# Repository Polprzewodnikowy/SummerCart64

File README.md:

# SummerCart64 - a fully open source N64 flashcart

**For non-technical description of the SummerCart64, please head to the https://summercart64.dev website!**

## Features

 - **ROM and Save Memory On-board**
   - 64 MiB SDRAM memory for game and save data (enough memory to support every retail game without compromise)
   - 16 MiB FLASH memory for bootloader and extended game data (with extended memory flashcart supports game ROMs up to 78 MiB)

 - **Game Saves**
   - EEPROM 4k/16k, SRAM and FlashRAM save types with an automatic writeback to the SD card (no reset button press required)

 - **Hardware-Dependent Game Features**
   - 64DD add-on emulation
   - Battery backed real time clock (RTC)

 - **Menu**
   - Dedicated open source menu written specifically for this flashcart - [N64FlashcartMenu](https://github.com/Polprzewodnikowy/N64FlashcartMenu)

 - **Game Development**
   - ~23.8 MiB/s peak transfer rate SD card interface
   - ~23.8 MiB/s peak transfer rate USB interface for data upload/download and debug functionality
   - PC app to access the flashcart features:
     - Game/save data upload/download
     - Feature enable control
     - Debug terminal
     - Access to the SD card
     - Firmware update
   - [UNFLoader](https://github.com/buu342/N64-UNFLoader) support
   - IS-Viewer 64 debug interface (fixed 64 kiB buffer with a movable base address)
   - 8 kiB on-chip buffer for general use
   - Status LED and button for general use
   - [UltraCIC_C](https://github.com/jago85/UltraCIC_C) emulation with automatic region switching and programmable seed/checksum values
   - N64 bootloader with support for IPL3 registers spoofing and loading menu from SD card

 - **Cartridge Production**
   - Initial programming via UART header or via dedicated JTAG/SWD interfaces
   - 3D printable shell

---

## Documentation

- [Quick startup guide](./docs/00_quick_startup_guide.md)
- [Memory map](./docs/01_memory_map.md)
- [N64 commands](./docs/02_n64_commands.md)
- [USB interface](./docs/03_usb_interface.md)
- [Config options](./docs/04_config_options.md)
- [FW and SW info](./docs/05_fw_and_sw_info.md)
- [Build guide](./docs/06_build_guide.md)

---

## How do I get one?

Most up to date information about purchasing/manufacturing options is available on https://summercart64.dev website!

If you want to order it yourself then I've prepared all necessary manufacturing files on the [PCBWay Shared Project](https://www.pcbway.com/project/member/shareproject/?bmbno=1046ED64-8AEE-44) site.

**Be careful**: this is an advanced project and it is assumed that you have enough knowledge about electronics.
Selecting wrong options or giving PCB manufacturer wrong information might result in an undesired time and/or money loss.
Boards also come unprogrammed from the manufacturer - you need to do **initial programming step** yourself after receiving the board.
**Price of the components is not included in the initial quote at the checkout** - manufacturer will contact you later with updated price.
To avoid problems _**please**_ read **both** [build guide](./docs/06_build_guide.md) and description on the shared project page **in full**.
If you have even slightest doubt about the ordering or programming process, it is better to leave it to someone experienced - ask in the [N64brew Discord server](https://discord.gg/8VNMKhxqQn) if that's the case.

**Full disclosure**: for every order made through [this link](https://www.pcbway.com/project/member/shareproject/?bmbno=1046ED64-8AEE-44) I will receive 10% of PCB manufacturing and PCB assembly service cost (price of the components is not included in the split). This is a great way of supporting further project development.

If you don't need a physical product but still want to support me then check the sponsor links on the [official website](https://summercart64.dev).

---

## High-level flashcart block diagram

---

## Finished example

---

## Acknowledgement

This project wouldn't be possible without these contributions:

- [64drive](https://64drive.retroactive.be) ([archived](https://web.archive.org/web/20240406215731/https://64drive.retroactive.be/)) orders being on permanent hold long before creating this repository.
- [EverDrive-64 X7](https://krikzz.com/our-products/cartridges/ed64x7.html) being disappointment for homebrew development (slow USB upload, unjustified price and overcomplicated SD card access).
  - Context: Both aforementioned products were priced at $199 in 2020. 64drive features made it a vastly more useful tool for homebrew development.
    Since then, 64drive had never been restocked and EverDrive-64 X7 price was lowered to $159 (as of May 2024).
- [Jan Goldacker (@jago85)](https://github.com/jago85) and his projects:
  - [Brutzelkarte](https://github.com/jago85/Brutzelkarte_FPGA) providing solid base for starting this project and sparking hope for true open source N64 flashcarts.
  - [UltraCIC_C](https://github.com/jago85/UltraCIC_C) reimplementation for easy integration in modern microcontrollers. Thanks also goes to everyone involved in N64 CIC reverse engineering.
- [N64brew](https://discord.gg/WqFgNWf) Discord server community being very helpful during flashcart development.
- [FatFs](http://elm-chan.org/fsw/ff/00index_e.html) FAT32/exFAT library being easiest to integrate in embedded environment.
- [Yakumono's (@LuigiBlood)](https://twitter.com/LuigiBlood) extensive [64DD documentation](https://github.com/LuigiBlood/64dd/wiki) and its implementation in various emulators.
- [Libdragon](https://github.com/DragonMinded/libdragon) open source N64 SDK project and its developers.
- [SERV](https://github.com/olofk/serv) bit-serial 32-bit RISC-V CPU soft core.

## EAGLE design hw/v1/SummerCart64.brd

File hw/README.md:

# SummerCart64 Hardware

Schematics and PCB design for SummerCart64 done in Autodesk Eagle software.

## TODO

- Expand documentation

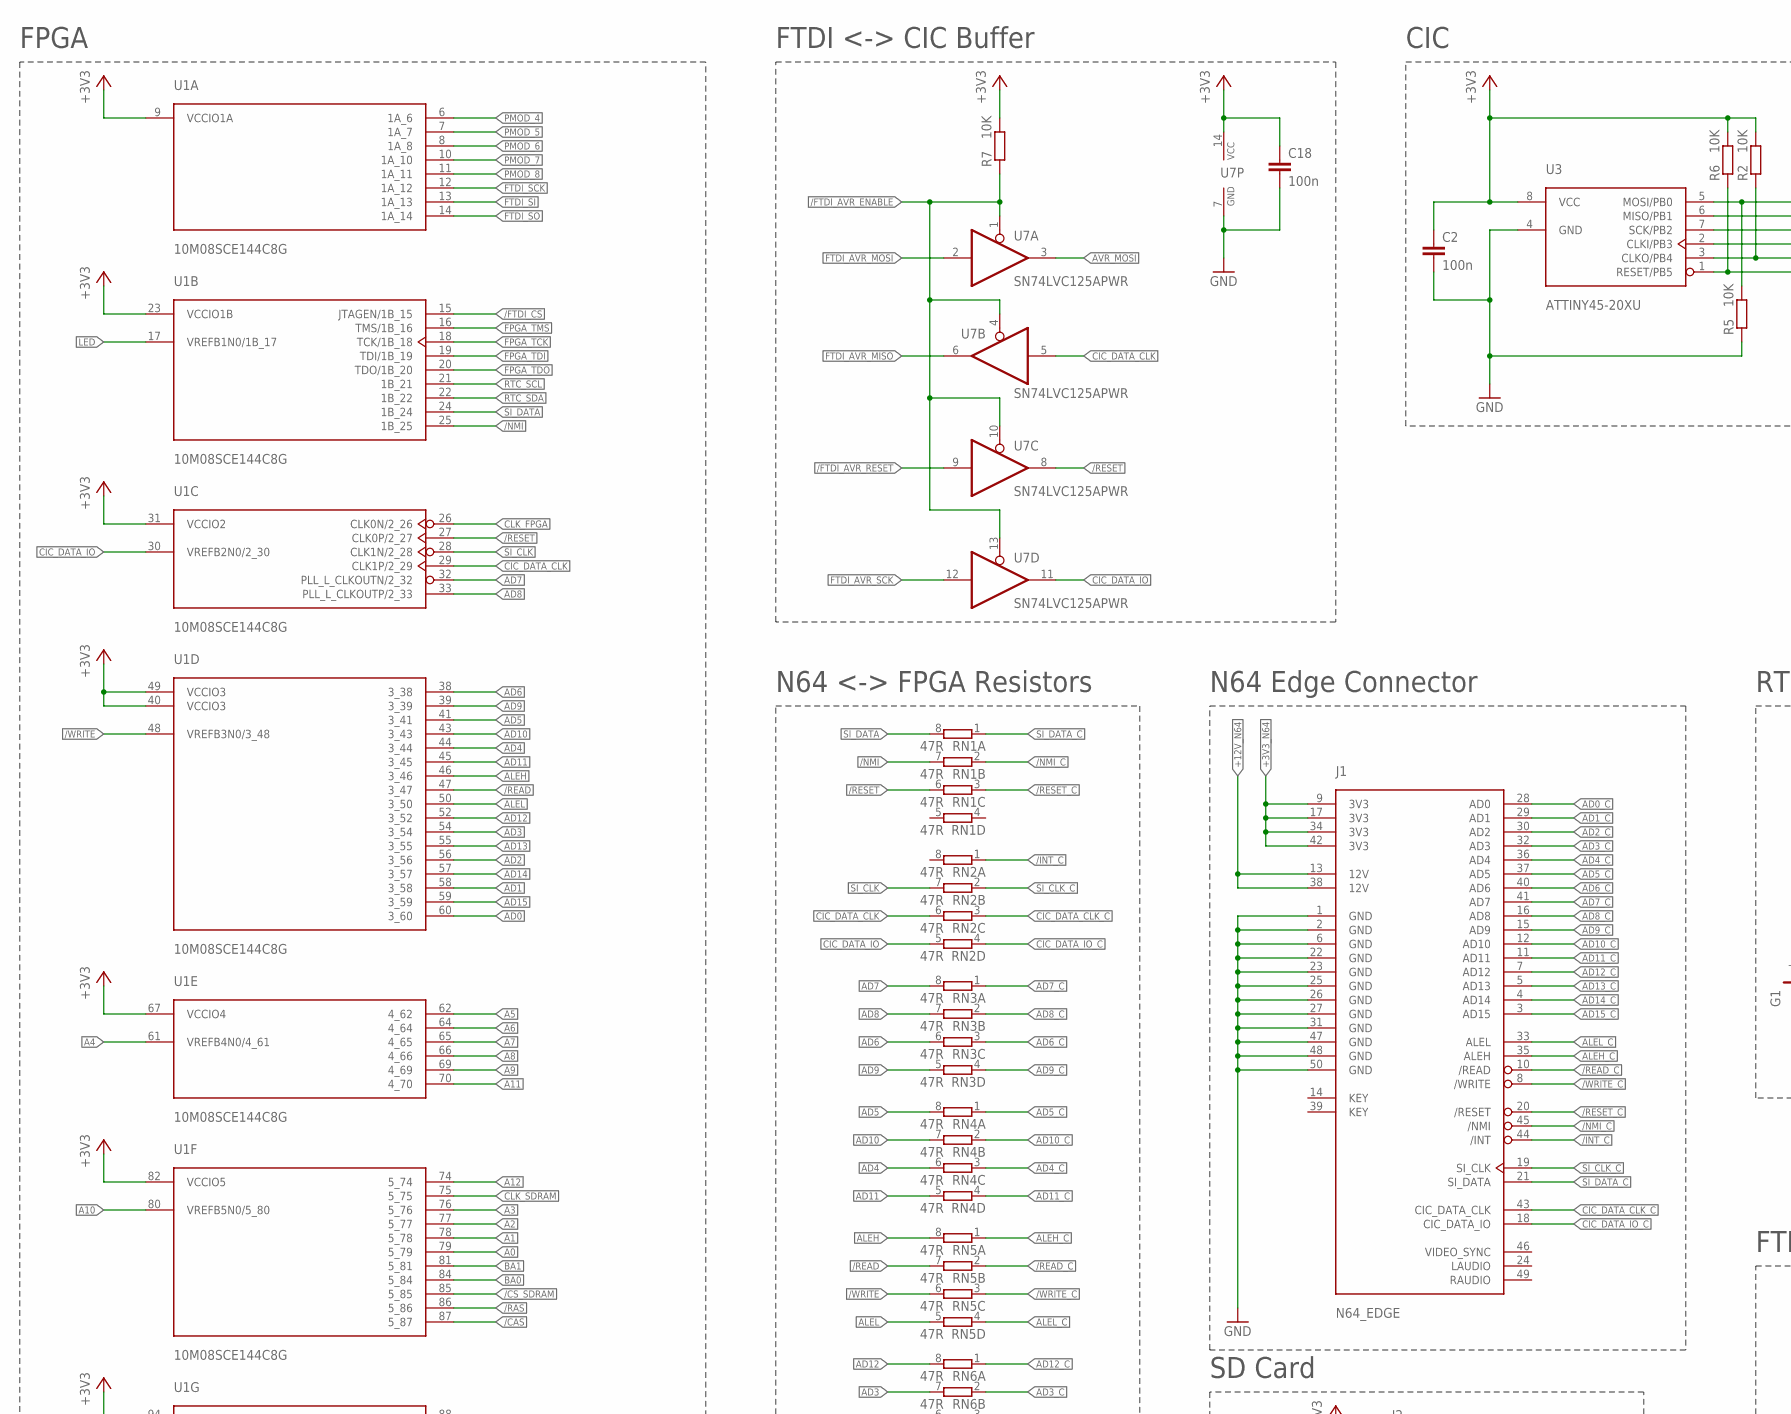
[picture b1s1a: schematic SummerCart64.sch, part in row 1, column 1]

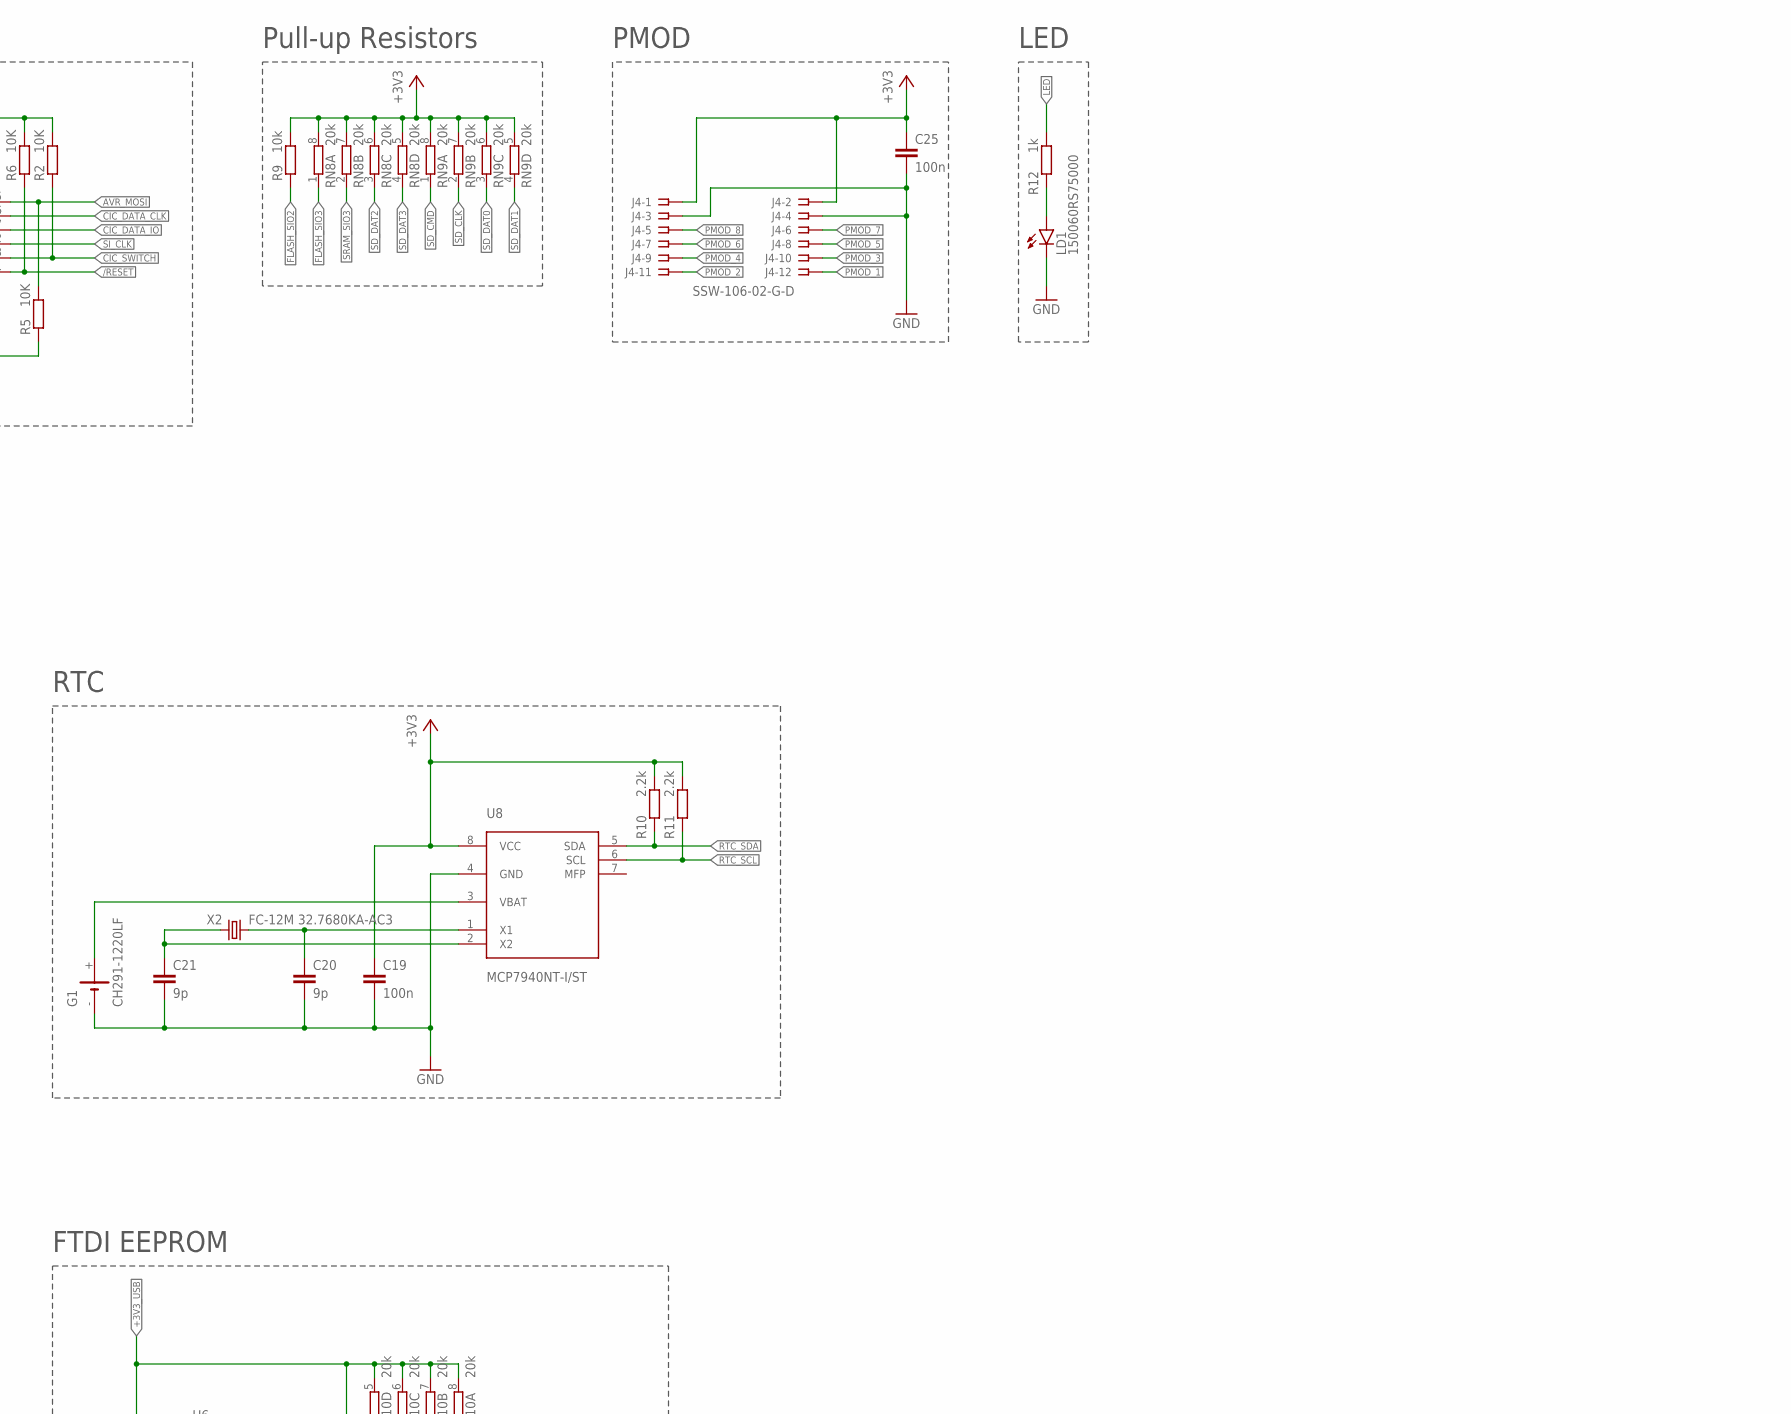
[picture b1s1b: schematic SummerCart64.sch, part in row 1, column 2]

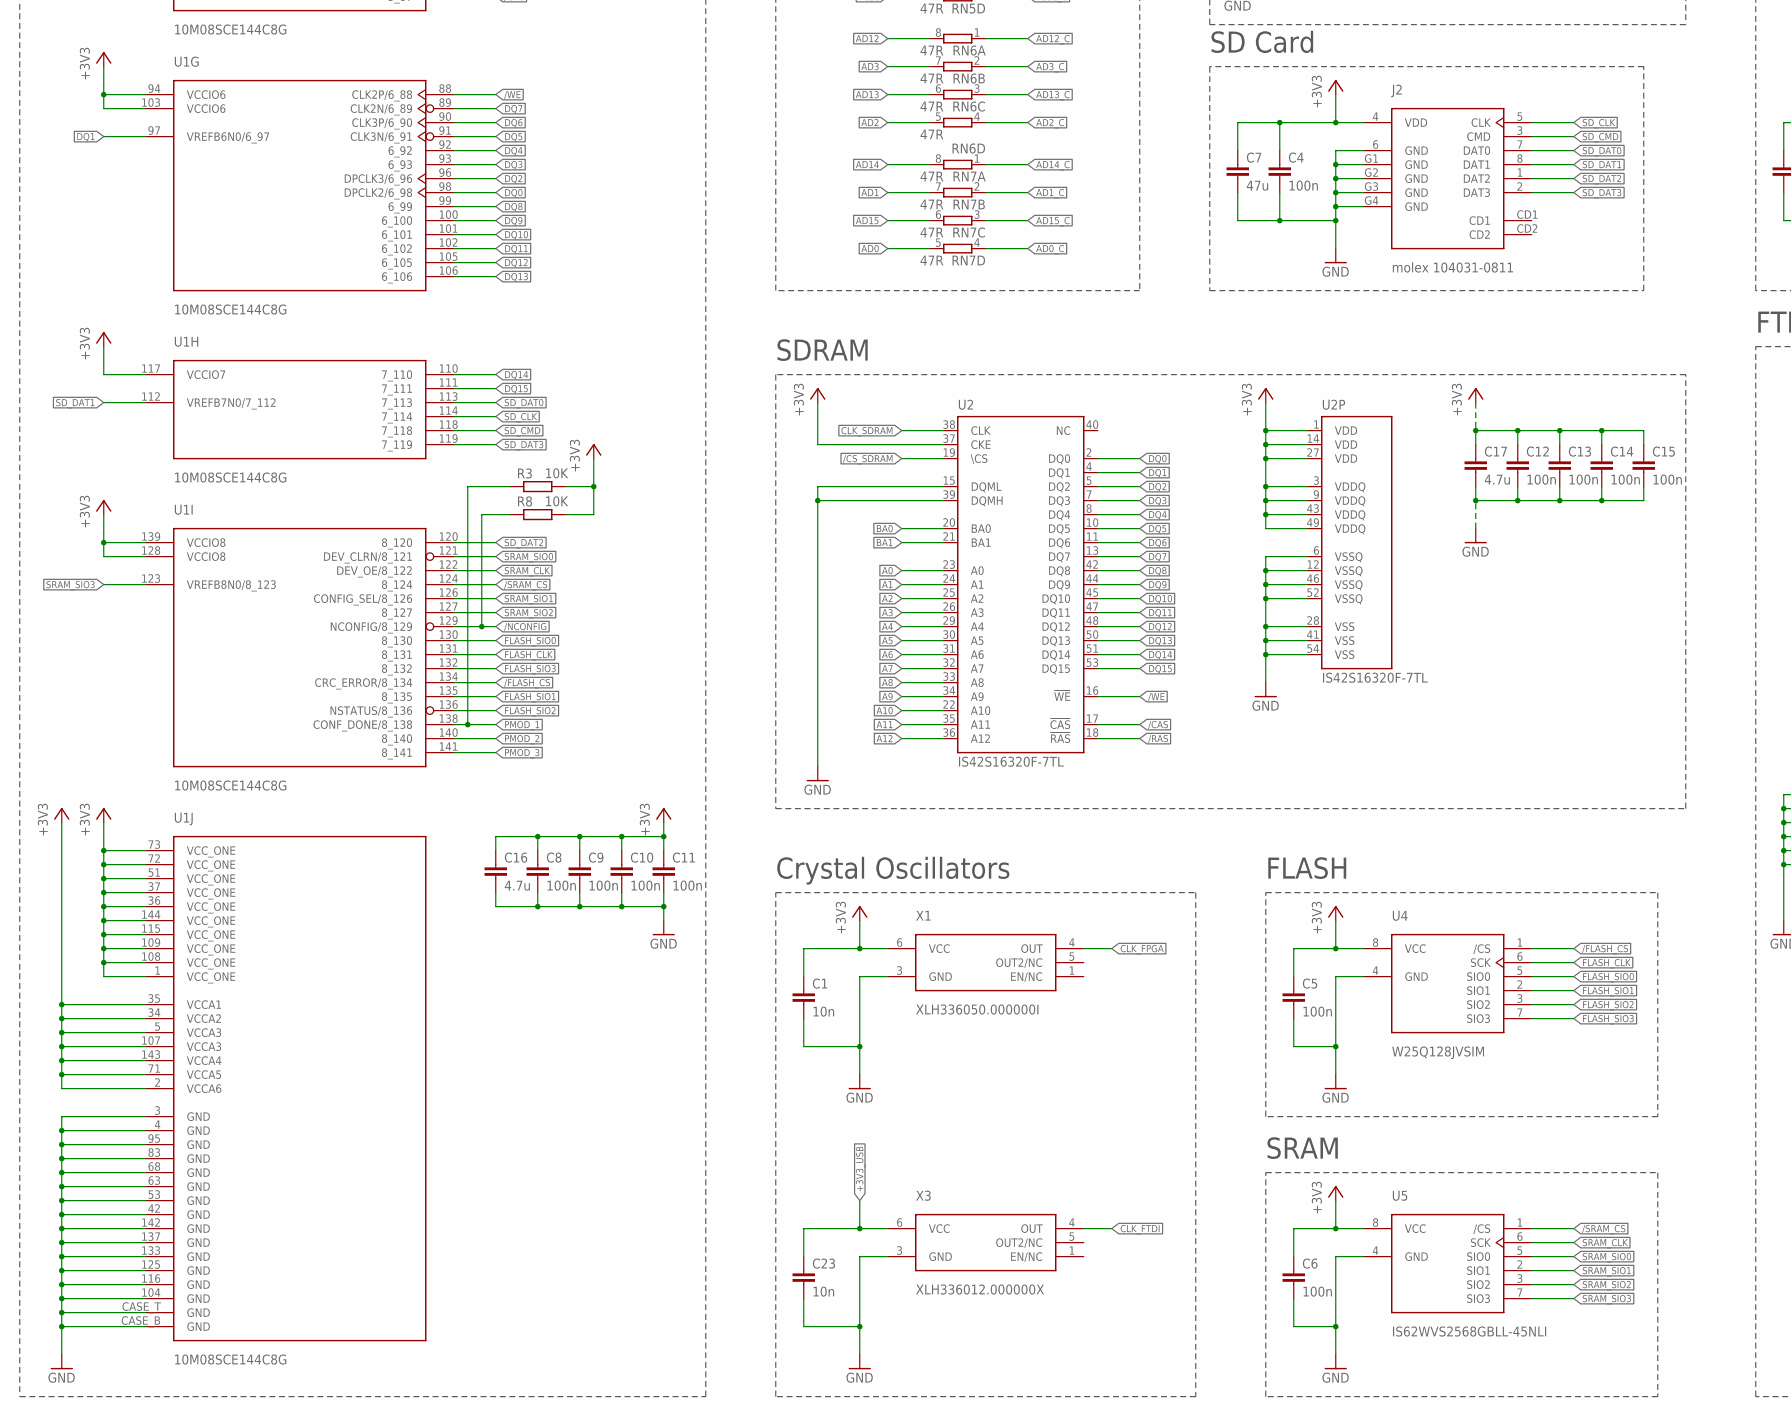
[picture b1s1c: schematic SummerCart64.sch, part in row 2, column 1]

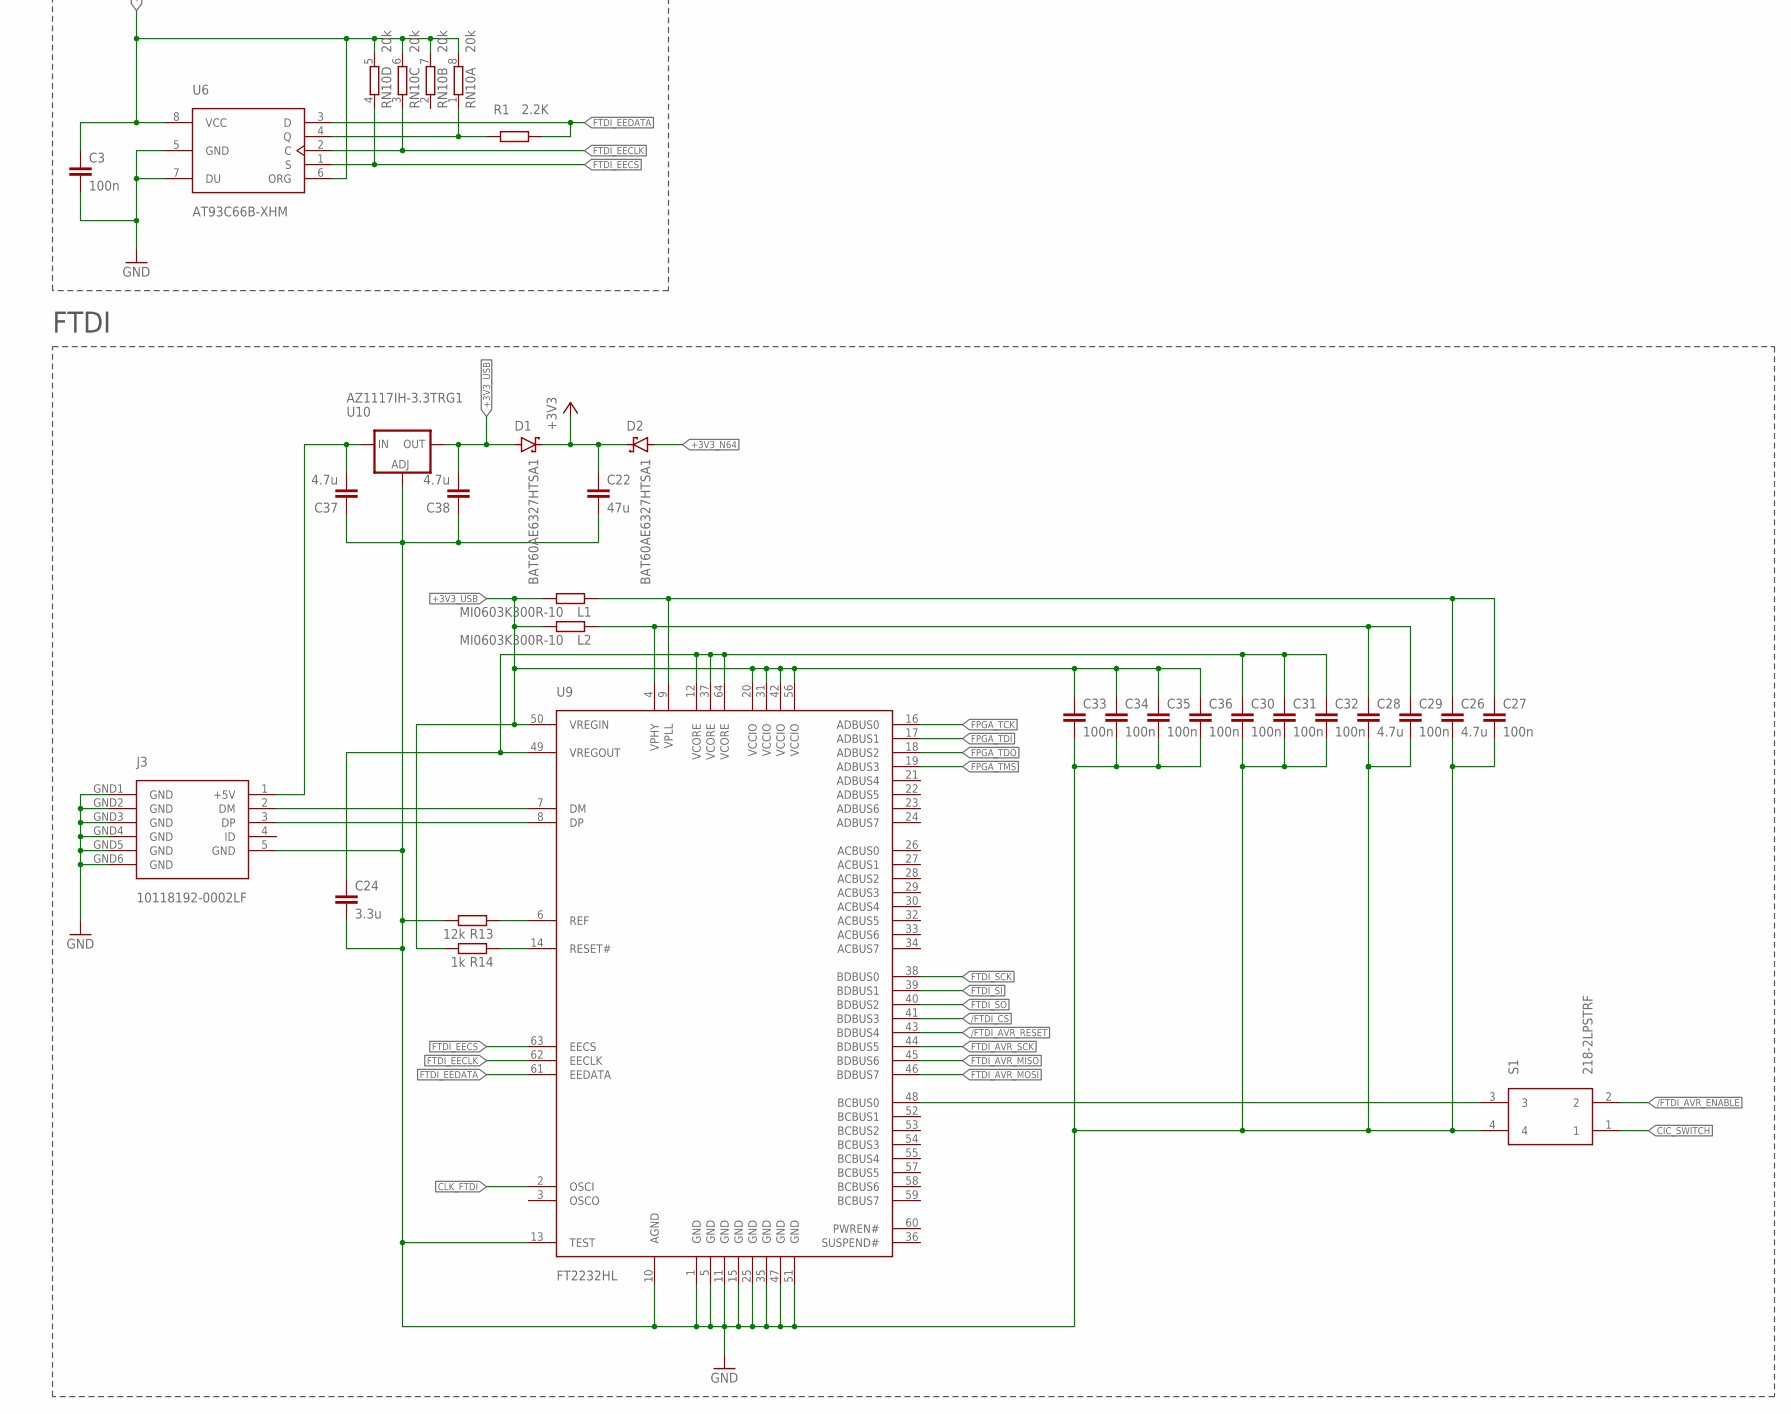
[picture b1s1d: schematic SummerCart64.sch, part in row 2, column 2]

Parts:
C1, C23: 10n; C0603
C2, C3, C4, C5, C6, C8, C9, C10, C11, C12, C13, C14, C15, C18, C19, C25, C27, C29, C30, C31, C32, C33, C34, C35, C36: 100n; C0603
C7, C22: 47u; C0805
C16, C17, C26, C28, C37, C38: 4.7u; C0603
C20, C21: 9p; C0603
C24: 3.3u; C0603
D1, D2: BAT60AE6327HTSA1; SOD323_ST
G1: CH291-1220LF
J1: N64_EDGE
J2: molex 104031-0811; MICRO_SD
J3: 10118192-0002LF; MICRO_USB
J4: SSW-106-02-G-D
L1, L2: MI0603K300R-10; R0603
LD1: 150060RS75000; SML0603
R1: 2.2K; R0603
R2, R3, R5, R6, R7, R8: 10K; R0603
R9: 10k; R0603
R10, R11: 2.2k; R0603
R12, R14: 1k; R0603
R13: 12k; R0603
RN1, RN2, RN3, RN4, RN5, RN6, RN7: 47R; CAY16
RN8, RN9, RN10: 20k; CAY16
S1: 218-2LPSTRF; 218-2
U1: 10M08SCE144C8G; EQFP144
U2: IS42S16320F-7TL; TSOP54-400
U3: ATTINY45-20XU; TSSOP8
U4: W25Q128JVSIM; SO8_208MIL
U5: IS62WVS2568GBLL-45NLI; SO8_150MIL
U6: AT93C66B-XHM; TSSOP8
U7: SN74LVC125APWR; TSSOP14
U8: MCP7940NT-I/ST; TSSOP8
U9: FT2232HL; LQFP64
U10: AZ1117IH-3.3TRG1; SOT223
X1: XLH336050.000000I; 3.2X2.5_OSCILLATOR
X2: FC-12M 32.7680KA-AC3; FC-12M
X3: XLH336012.000000X; 3.2X2.5_OSCILLATOR

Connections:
+1.8V_USB: C24.1, C30.1, C31.1, C32.1, U9.12 (VCORE), U9.37 (VCORE), U9.49 (VREGOUT), U9.64 (VCORE)
+3V3: C1.1, C2.1, C4.1, C5.1, C6.1, C7.1, C8.1, C9.1, C10.1, C11.1, C12.1, C13.1, C14.1, C15.1, C16.1, C17.1, C18.1, C19.1, C22.1, C25.1, D1.C, D2.C, J2.4 (VDD), J4.1, J4.2, R2.2, R3.2, R6.2, R7.2, R8.2, R9.2, R10.2, R11.2, RN8.5 (2), RN8.6 (2), RN8.7 (2), RN8.8 (2), RN9.5 (2), RN9.6 (2), RN9.7 (2), RN9.8 (2), U1.1 (VCC_ONE), U1.2 (VCCA6), U1.5 (VCCA3), U1.9 (VCCIO1A), U1.23 (VCCIO1B), U1.31 (VCCIO2), U1.34 (VCCA2), U1.35 (VCCA1), U1.36 (VCC_ONE), U1.37 (VCC_ONE), U1.40 (VCCIO3), U1.49 (VCCIO3), U1.51 (VCC_ONE), U1.67 (VCCIO4), U1.71 (VCCA5), U1.72 (VCC_ONE), U1.73 (VCC_ONE), U1.82 (VCCIO5), U1.94 (VCCIO6), U1.103 (VCCIO6), U1.107 (VCCA3), U1.108 (VCC_ONE), U1.109 (VCC_ONE), U1.115 (VCC_ONE), U1.117 (VCCIO7), U1.128 (VCCIO8), U1.139 (VCCIO8), U1.143 (VCCA4), U1.144 (VCC_ONE), U2.1 (VDD), U2.3 (VDDQ), U2.9 (VDDQ), U2.14 (VDD), U2.27 (VDD), U2.37 (CKE), U2.43 (VDDQ), U2.49 (VDDQ), U3.8 (VCC), U4.8 (VCC), U5.8 (VCC), U7.14 (VCC), U8.8 (VCC), X1.6 (VCC)
+3V3_N64: D2.A, J1.9 (3V3), J1.17 (3V3), J1.34 (3V3), J1.42 (3V3)
+3V3_USB: C3.1, C23.1, C33.1, C34.1, C35.1, C36.1, C38.2, D1.A, L1.2, L2.2, R14.2, RN10.5 (2), RN10.6 (2), RN10.7 (2), RN10.8 (2), U6.6 (ORG), U6.8 (VCC), U9.20 (VCCIO), U9.31 (VCCIO), U9.42 (VCCIO), U9.50 (VREGIN), U9.56 (VCCIO), U10.4 (OUT), X3.6 (VCC)
+5V_USB: C37.2, J3.1 (+5V), U10.3 (IN)
+12V_N64: J1.13 (12V), J1.38 (12V)
/CAS: U1.87 (5_87), U2.17 (!CAS)
/CS_SDRAM: U1.85 (5_85), U2.19 (\CS)
/FLASH_CS: U1.134 (CRC_ERROR/8_134), U4.1 (/CS)
/FTDI_AVR_ENABLE: R7.1, S1.2, U7.1 (OE), U7.4 (OE), U7.10 (OE), U7.13 (OE)
/FTDI_AVR_RESET: U7.9 (I), U9.43 (BDBUS4)
/FTDI_CS: U1.15 (JTAGEN/1B_15), U9.41 (BDBUS3)
/INT_C: J1.44 (/INT), RN2.1
/NCONFIG: R8.1, U1.129 (NCONFIG/8_129)
/NMI: RN1.7 (2), U1.25 (1B_25)
/NMI_C: J1.45 (/NMI), RN1.2 (1)
/RAS: U1.86 (5_86), U2.18 (!RAS)
/READ: RN5.7 (2), U1.47 (3_47)
/READ_C: J1.10 (/READ), RN5.2 (1)
/RESET: R6.1, RN1.6 (2), U1.27 (CLK0P/2_27), U3.1 (RESET/PB5), U7.8 (O)
/RESET_C: J1.20 (/RESET), RN1.3 (1)
/SRAM_CS: U1.124 (8_124), U5.1 (/CS)
/WE: U1.88 (CLK2P/6_88), U2.16 (!WE)
/WRITE: RN5.6 (2), U1.48 (VREFB3N0/3_48)
/WRITE_C: J1.8 (/WRITE), RN5.3 (1)
A0: U1.79 (5_79), U2.23 (A0)
A1: U1.78 (5_78), U2.24 (A1)
A2: U1.77 (5_77), U2.25 (A2)
A3: U1.76 (5_76), U2.26 (A3)
A4: U1.61 (VREFB4N0/4_61), U2.29 (A4)
A5: U1.62 (4_62), U2.30 (A5)
A6: U1.64 (4_64), U2.31 (A6)
A7: U1.65 (4_65), U2.32 (A7)
A8: U1.66 (4_66), U2.33 (A8)
A9: U1.69 (4_69), U2.34 (A9)
A10: U1.80 (VREFB5N0/5_80), U2.22 (A10)
A11: U1.70 (4_70), U2.35 (A11)
A12: U1.74 (5_74), U2.36 (A12)
AD0: RN7.5 (2), U1.60 (3_60)
AD0_C: J1.28 (AD0), RN7.4 (1)
AD1: RN7.7 (2), U1.58 (3_58)
AD1_C: J1.29 (AD1), RN7.2 (1)
AD2: RN6.5 (2), U1.56 (3_56)
AD2_C: J1.30 (AD2), RN6.4 (1)
AD3: RN6.7 (2), U1.54 (3_54)
AD3_C: J1.32 (AD3), RN6.2 (1)
AD4: RN4.6 (2), U1.44 (3_44)
AD4_C: J1.36 (AD4), RN4.3 (1)
AD5: RN4.8 (2), U1.41 (3_41)
AD5_C: J1.37 (AD5), RN4.1
AD6: RN3.6 (2), U1.38 (3_38)
AD6_C: J1.40 (AD6), RN3.3 (1)
AD7: RN3.8 (2), U1.32 (PLL_L_CLKOUTN/2_32)
AD7_C: J1.41 (AD7), RN3.1
AD8: RN3.7 (2), U1.33 (PLL_L_CLKOUTP/2_33)
AD8_C: J1.16 (AD8), RN3.2 (1)
AD9: RN3.5 (2), U1.39 (3_39)
AD9_C: J1.15 (AD9), RN3.4 (1)
AD10: RN4.7 (2), U1.43 (3_43)
AD10_C: J1.12 (AD10), RN4.2 (1)
AD11: RN4.5 (2), U1.45 (3_45)
AD11_C: J1.11 (AD11), RN4.4 (1)
AD12: RN6.8 (2), U1.52 (3_52)
AD12_C: J1.7 (AD12), RN6.1
AD13: RN6.6 (2), U1.55 (3_55)
AD13_C: J1.5 (AD13), RN6.3 (1)
AD14: RN7.8 (2), U1.57 (3_57)
AD14_C: J1.4 (AD14), RN7.1
AD15: RN7.6 (2), U1.59 (3_59)
AD15_C: J1.3 (AD15), RN7.3 (1)
ALEH: RN5.8 (2), U1.46 (3_46)
ALEH_C: J1.35 (ALEH), RN5.1
ALEL: RN5.5 (2), U1.50 (3_50)
ALEL_C: J1.33 (ALEL), RN5.4 (1)
AVR_MOSI: R5.2, U3.5 (MOSI/PB0), U7.3 (O)
BA0: U1.84 (5_84), U2.20 (BA0)
BA1: U1.81 (5_81), U2.21 (BA1)
CIC_DATA_CLK: RN2.6 (2), U1.29 (CLK1P/2_29), U3.6 (MISO/PB1), U7.5 (I)
CIC_DATA_CLK_C: J1.43 (CIC_DATA_CLK), RN2.3 (1)
CIC_DATA_IO: RN2.5 (2), U1.30 (VREFB2N0/2_30), U3.7 (SCK/PB2), U7.11 (O)
CIC_DATA_IO_C: J1.18 (CIC_DATA_IO), RN2.4 (1)
CIC_SWITCH: R2.1, S1.1, U3.3 (CLKO/PB4)
CLK_FPGA: U1.26 (CLK0N/2_26), X1.4 (OUT)
CLK_FTDI: U9.2 (OSCI), X3.4 (OUT)
CLK_SDRAM: U1.75 (5_75), U2.38 (CLK)
DQ0: U1.98 (DPCLK2/6_98), U2.2 (DQ0)
DQ1: U1.97 (VREFB6N0/6_97), U2.4 (DQ1)
DQ2: U1.96 (DPCLK3/6_96), U2.5 (DQ2)
DQ3: U1.93 (6_93), U2.7 (DQ3)
DQ4: U1.92 (6_92), U2.8 (DQ4)
DQ5: U1.91 (CLK3N/6_91), U2.10 (DQ5)
DQ6: U1.90 (CLK3P/6_90), U2.11 (DQ6)
DQ7: U1.89 (CLK2N/6_89), U2.13 (DQ7)
DQ8: U1.99 (6_99), U2.42 (DQ8)
DQ9: U1.100 (6_100), U2.44 (DQ9)
DQ10: U1.101 (6_101), U2.45 (DQ10)
DQ11: U1.102 (6_102), U2.47 (DQ11)
DQ12: U1.105 (6_105), U2.48 (DQ12)
DQ13: U1.106 (6_106), U2.50 (DQ13)
DQ14: U1.110 (7_110), U2.51 (DQ14)
DQ15: U1.111 (7_111), U2.53 (DQ15)
D_N: J3.2 (DM), U9.7 (DM)
D_P: J3.3 (DP), U9.8 (DP)
FLASH_CLK: U1.131 (8_131), U4.6 (SCK)
FLASH_SIO0: U1.130 (8_130), U4.5 (SIO0)
FLASH_SIO1: U1.135 (8_135), U4.2 (SIO1)
FLASH_SIO2: R9.1, U1.136 (NSTATUS/8_136), U4.3 (SIO2)
FLASH_SIO3: RN8.1, U1.132 (8_132), U4.7 (SIO3)
FPGA_TCK: U1.18 (TCK/1B_18), U9.16 (ADBUS0)
FPGA_TDI: U1.19 (TDI/1B_19), U9.17 (ADBUS1)
FPGA_TDO: U1.20 (TDO/1B_20), U9.18 (ADBUS2)
FPGA_TMS: U1.16 (TMS/1B_16), U9.19 (ADBUS3)
FTDI_AVR_MISO: U7.6 (O), U9.45 (BDBUS6)
FTDI_AVR_MOSI: U7.2 (I), U9.46 (BDBUS7)
FTDI_AVR_SCK: U7.12 (I), U9.44 (BDBUS5)
FTDI_EECLK: RN10.3 (1), U6.2 (C), U9.62 (EECLK)
FTDI_EECS: RN10.4 (1), U6.1 (S), U9.63 (EECS)
FTDI_EEDATA: R1.2, U6.3 (D), U9.61 (EEDATA)
FTDI_REF: R13.1, U9.6 (REF)
FTDI_RESET: R14.1, U9.14 (RESET#)
FTDI_SCK: U1.12 (1A_12), U9.38 (BDBUS0)
FTDI_SI: U1.13 (1A_13), U9.39 (BDBUS1)
FTDI_SO: U1.14 (1A_14), U9.40 (BDBUS2)
FTDI_VPHY: C28.1, C29.1, L2.1, U9.4 (VPHY)
FTDI_VPLL: C26.1, C27.1, L1.1, U9.9 (VPLL)
GND: C1.2, C2.2, C3.2, C4.2, C5.2, C6.2, C7.2, C8.2, C9.2, C10.2, C11.2, C12.2, C13.2, C14.2, C15.2, C16.2, C17.2, C18.2, C19.2, C20.2, C21.2, C22.2, C23.2, C24.2, C25.2, C26.2, C27.2, C28.2, C29.2, C30.2, C31.2, C32.2, C33.2, C34.2, C35.2, C36.2, C37.1, C38.1, G1.-, J1.1 (GND), J1.2 (GND), J1.6 (GND), J1.22 (GND), J1.23 (GND), J1.25 (GND), J1.26 (GND), J1.27 (GND), J1.31 (GND), J1.47 (GND), J1.48 (GND), J1.50 (GND), J2.6 (GND), J2.G1 (GND), J2.G2 (GND), J2.G3 (GND), J2.G4 (GND), J3.5 (GND), J3.GND1 (GND), J3.GND2 (GND), J3.GND3 (GND), J3.GND4 (GND), J3.GND5 (GND), J3.GND6 (GND), J4.3, J4.4, LD1.C, R5.1, R13.2, S1.4, U1.3 (GND), U1.4 (GND), U1.42 (GND), U1.53 (GND), U1.63 (GND), U1.68 (GND), U1.83 (GND), U1.95 (GND), U1.104 (GND), U1.116 (GND), U1.125 (GND), U1.133 (GND), U1.137 (GND), U1.142 (GND), U1.CASE_B (GND), U1.CASE_T (GND), U2.6 (VSSQ), U2.12 (VSSQ), U2.15 (DQML), U2.28 (VSS), U2.39 (DQMH), U2.41 (VSS), U2.46 (VSSQ), U2.52 (VSSQ), U2.54 (VSS), U3.4 (GND), U4.4 (GND), U5.4 (GND), U6.5 (GND), U6.7 (DU), U7.7 (GND), U8.4 (GND), U9.1 (GND), U9.5 (GND), U9.10 (AGND), U9.11 (GND), U9.13 (TEST), U9.15 (GND), U9.25 (GND), U9.35 (GND), U9.47 (GND), U9.51 (GND), U10.1 (ADJ), X1.3 (GND), X3.3 (GND)
LED: R12.2, U1.17 (VREFB1N0/1B_17)
unnamed: S1.3, U9.48 (BCBUS0)
unnamed: LD1.A, R12.1
unnamed: R1.1, RN10.1, U6.4 (Q)
PMOD_1: J4.12, R3.1, U1.138 (CONF_DONE/8_138)
PMOD_2: J4.11, U1.140 (8_140)
PMOD_3: J4.10, U1.141 (8_141)
PMOD_4: J4.9, U1.6 (1A_6)
PMOD_5: J4.8, U1.7 (1A_7)
PMOD_6: J4.7, U1.8 (1A_8)
PMOD_7: J4.6, U1.10 (1A_10)
PMOD_8: J4.5, U1.11 (1A_11)
RTC_SCL: R11.1, U1.21 (1B_21), U8.6 (SCL)
RTC_SDA: R10.1, U1.22 (1B_22), U8.5 (SDA)
RTC_VBAT: G1.+, U8.3 (VBAT)
RTC_X1: C20.1, U8.1 (X1), X2.2
RTC_X2: C21.1, U8.2 (X2), X2.1
SD_CLK: J2.5 (CLK), RN9.2 (1), U1.114 (7_114)
SD_CMD: J2.3 (CMD), RN9.1, U1.118 (7_118)
SD_DAT0: J2.7 (DAT0), RN9.3 (1), U1.113 (7_113)
SD_DAT1: J2.8 (DAT1), RN9.4 (1), U1.112 (VREFB7N0/7_112)
SD_DAT2: J2.1 (DAT2), RN8.3 (1), U1.120 (8_120)
SD_DAT3: J2.2 (DAT3), RN8.4 (1), U1.119 (7_119)
SI_CLK: RN2.7 (2), U1.28 (CLK1N/2_28), U3.2 (CLKI/PB3)
SI_CLK_C: J1.19 (SI_CLK), RN2.2 (1)
SI_DATA: RN1.8 (2), U1.24 (1B_24)
SI_DATA_C: J1.21 (SI_DATA), RN1.1
SRAM_CLK: U1.122 (DEV_OE/8_122), U5.6 (SCK)
SRAM_SIO0: U1.121 (DEV_CLRN/8_121), U5.5 (SIO0)
SRAM_SIO1: U1.126 (CONFIG_SEL/8_126), U5.2 (SIO1)
SRAM_SIO2: U1.127 (8_127), U5.3 (SIO2)
SRAM_SIO3: RN8.2 (1), U1.123 (VREFB8N0/8_123), U5.7 (SIO3)

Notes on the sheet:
RTC
LED
CIC
PMOD
FLASH
SRAM
FTDI EEPROM
N64 <-> FPGA Resistors
N64 Edge Connector
Crystal Oscillators
SDRAM
FTDI <-> CIC Buffer
FPGA
Pull-up Resistors
SD Card
FTDI

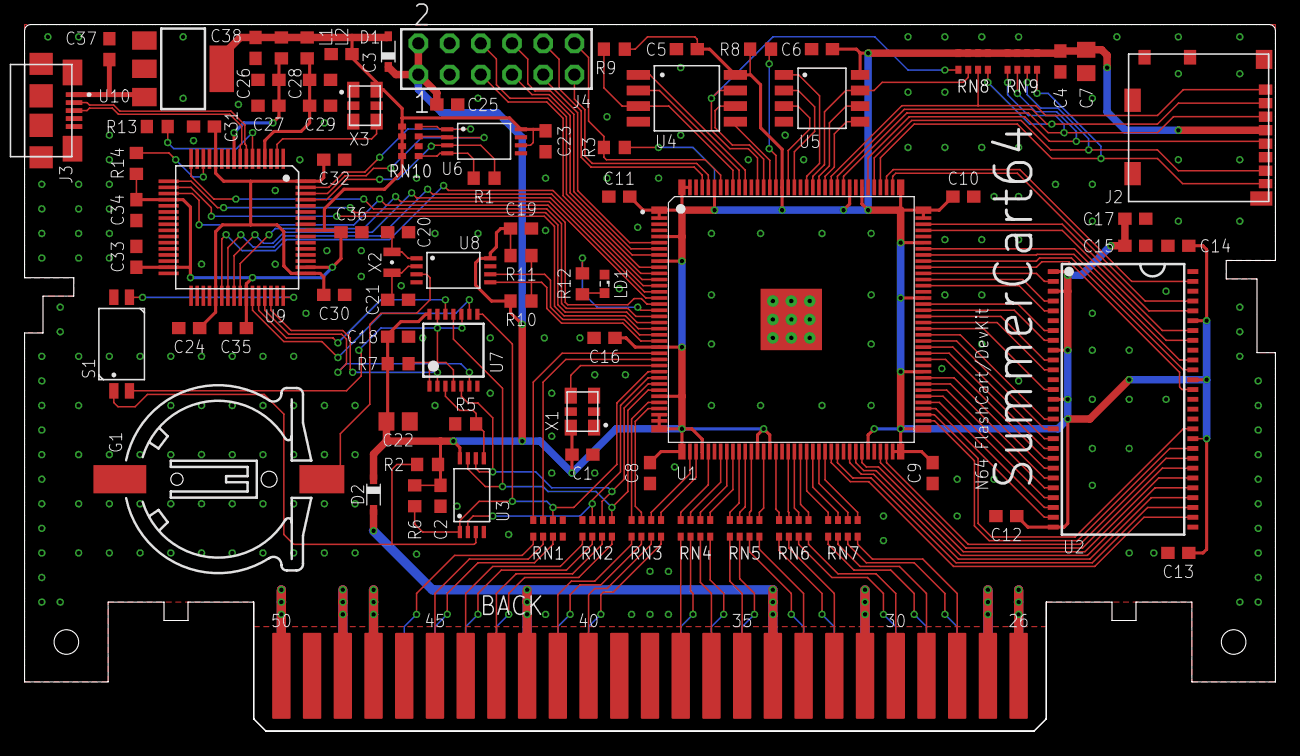
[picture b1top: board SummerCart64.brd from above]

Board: 2 copper layers, 101.8 x 57.5 mm, 85 parts (0 on the bottom side), 158 nets.

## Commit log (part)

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2026-03-28 Fix SC64 SD read: use physical address for DMA + cache invalidate
    SC64 firmware does DMA directly to RDRAM using physical addresses.
    Our code passed KSEG0 virtual address (0x80xxxxxx) but SC64 needs
    physical (0x00xxxxxx). Fixed: strip upper 3 bits with & 0x1FFFFFFF.
    Also: invalidate data cache after DMA so CPU sees the new data
    (SC64 writes to RDRAM bypassing CPU cache).
    https://claude.ai/code/session_01RAifKp5aeprBiRruyxTAdk
2026-03-28 Portal BFS room traversal + per-vertex Gouraud shading — CAVES RENDERING ON N64
    First ever Tomb Raider 1 level geometry rendered on Nintendo 64.
    Real .PHD level data from the original 1996 game, parsed and drawn
    on real N64 hardware via SC64 flashcart.
    - BFS portal traversal renders all connected rooms (up to 60)
    - Per-vertex Gouraud shading from original TR1 light values
    - Free-fly camera with analog stick
2026-03-28 Pre-convert all textures to 16x16 RGBA16 at load time
    - Eliminates ALL per-frame texture conversion and buffer reuse issues
    - Each object texture gets its own permanent RGBA16 surface in heap
    - No CI8/TLUT complexity — pure RGBA16 with bilinear filtering
    - Render loop just calls rdpq_tex_upload with pre-made surface
    - ~1MB for ~2000 textures (16x16x2 bytes each)
    - UV coords pre-computed at load time per texture
2026-03-28 Add Lara model rendering with bone tree traversal
    Renders Lara's 3D mesh at her spawn position using the full bone
    hierarchy (push/pop matrix stack). Decodes first animation frame
    for the T-pose rotations. Each of her ~15 body part meshes is
    transformed through the bone tree and drawn with the same textured
    triangle pipeline as rooms. Lara is drawn fully lit (shade=1.0)
    after rooms for proper depth ordering.
2026-03-28 Fix room loading: track camera room in both fly and walk modes
    Room detection was inside the walk_mode block, so in fly mode
    lara_room never updated and BFS always showed the same rooms.
    Now room tracking always runs — new rooms load as you explore.
    https://claude.ai/code/session_01RAifKp5aeprBiRruyxTAdk
2026-03-28 D-pad up/down = fly up/down, C-buttons = move/strafe
    D-pad: up/down fly vertically, left/right strafe
    C-buttons: up/down move forward/back, left/right strafe
    https://claude.ai/code/session_01RAifKp5aeprBiRruyxTAdk
2026-03-28 Anti-aliasing: VI edge filter + RDP per-triangle AA
    - VI: FILTERS_RESAMPLE_ANTIALIAS (divot filter for edge smoothing)
    - RDP: AA_STANDARD for per-pixel coverage-based anti-aliasing
    - Both applied to all geometry (rooms, Lara, items, static objects)
    - Should smooth jagged edges on Lara's legs and all triangle edges
    https://claude.ai/code/session_01RAifKp5aeprBiRruyxTAdk
2026-03-29 Wire up actual sound playback through libdragon mixer
    - Created pcm_wave_t wrapper for in-memory PCM → waveform_t
    - Cycles through parsed TR1 samples, plays one every ~7 seconds
    - Uses mixer channel 0 at 50% volume
    - Cache flush before playback for DMA coherency
    - Should hear actual TR1 cave ambient sound effects!
    https://claude.ai/code/session_01RAifKp5aeprBiRruyxTAdk
2026-03-29 Wall collision: 512-unit probe ahead + audio debug on pause
    - Wall collision now probes 512 units ahead of destination to catch
    thin wall sectors that fast movement could skip over
    - Wall slide tries X-only then Z-only when blocked
    - Pause screen now shows full sound data debug: sample_data pointer,
    sizes, index count, flags, compressed/full sizes
    - This helps diagnose why audio shows 0 samples
2026-03-29 Debug: disable textures/fog to test GL geometry only
    Temporarily disabled GL textures and fog to isolate whether the
    garbled rendering is a geometry/projection issue or a texture issue.
    Should show flat-shaded cave with vertex colors only.
    https://claude.ai/code/session_01RAifKp5aeprBiRruyxTAdk
2026-03-29 Interleaved verts, more rooms, clamp textures, re-enable pause
    Performance + quality:
    - Interleaved vertex struct (24 bytes: 3f pos + 4ub color + 2f tc)
    Single cache flush instead of 3 separate arrays
    - GLubyte colors instead of GLfloat (4 bytes vs 16 bytes/vertex)
    - Per-face distance cull (12K unit radius) to skip far geometry
    - 16 rooms via portal BFS (was 5) to reduce pop-in
2026-03-29 Fix sparse textures: disable face decimation and revert fog
    Face decimation (f += face_skip) caused visible black holes because:
    1. Faces are sorted by texture — skipping every Nth face breaks
    texture batching and leaves gaps in spatial coverage
    2. Dark fog color (R=0.08) made distant faces appear nearly black
    Fixes:
    - Disable face_skip in render loop (always f++ for all faces)
2026-03-29 Phase 3: Textured RDPQ far pass with TMEM uploads
    Far pass now renders textured + shaded triangles via rdpq:
    - TRIFMT_SHADE_TEX format: {X, Y, R, G, B, A, S, T, INV_W}
    - rdpq_tex_upload(TILE0, &tex_surfs[idx], NULL) for each texture
    - Texture batching: only uploads when texture index changes
    (faces are pre-sorted by texture from load time)
    - Tex coords in pixel space (matching rdpq convention)
2026-03-29 Fix black gaps + OOM: disable face decimation, use rspq_wait
    1. Black gaps in far pass: face decimation (skip every Nth face)
    caused visible holes because faces are texture-sorted, not
    spatially sorted. Disabled — all far faces now draw.
    2. OOM: switched from rspq_flush (non-blocking send) to rspq_wait
    (blocking drain) at three points:
    - Before every texture upload
2026-03-29 On-demand mip generation for far pass
    Instead of pre-allocating mip surfaces for all 880 textures (OOM'd
    at 560KB uncached), generate mips on-the-fly for just the ~8
    textures uploaded per frame.
    Implementation:
    - One reusable 16×16 RGBA16 buffer = 512 bytes uncached
    - Box-filter 32→16 (2×2 average) computed on each far upload
2026-03-29 Lambert-style mip system: two LOD levels + fallback chain
    Following James Lambert's N64 optimization techniques:
    Mip levels:
    - Level 0: 32×32 base (near/overlap, full TMEM: 2048 bytes)
    - Level 1: 16×16 on-demand (mid distance, 512 bytes TMEM)
    - Level 2: 8×8 on-demand (very far, 128 bytes TMEM)
    Two reusable uncached buffers: 512 + 128 = 640 bytes total.
2026-03-29 Fix cave void + static mesh flicker
    1. Portal near-plane crossing: when a portal has some vertices
    behind the camera and some in front, the projected screen rect
    only covered the in-front vertices (too small). The portal
    actually spans the entire parent clip region when it crosses
    the near plane. Fix: expand to parent clip rect when any
    portal vertex is behind camera.
2026-03-29 Factor portal connectivity into per-room draw distance
    Rooms with more portal connections (junction areas) get a draw
    distance boost of ~1 sector per portal. This keeps important
    connecting rooms visible longer while small dead-end rooms still
    cull early.
    https://claude.ai/code/session_01CRpPKHXrP3YxsjPEStD62Z
2026-03-29 Performance: texture sort + back-cull + bind budget
    Three optimizations targeting the 73 texture binds / 7 FPS bottleneck:
    1. Sort faces by texture at load time (insertion sort per room).
    Groups same-texture faces together so consecutive faces share
    the same bind. Converts ~73 binds → ~15-20 unique textures.
    2. Per-face back-cull in GL near pass. Check first vertex depth
    (camera-space Z) before any vertex processing. Faces behind
2026-03-29 Fix Lara head, screen edge culling, save 704KB heap via zero-copy tex_pages
    Lara head invisible:
    - Changed z-reject (rz < 32 → vis=false; break) to z-clamp
    (rz < 4 → rz = 4). The old reject dropped entire faces if ANY
    vertex was close to camera. Head mesh vertices in 3rd-person view
    could be within 32 units, causing the whole head to vanish.
    - Exempt Lara from NEAR_FACE_BUDGET — she's fixed cost (~6ms) and
2026-03-29 Add portal64-still-alive to research log
    Key borrowable techniques:
    - Doorway frustum narrowing (construct per-portal frustum, recurse
    with tighter bounds — directly maps to TR1 room portals)
    - 4-bit twoTone textures (4bpp grayscale + combiner colorize =
    512B/tile vs 1KB CI8 — halves TMEM usage)
    - Pre-computed room non-visibility bitmask
2026-03-30 Fix uninitialized variable warnings for effective budgets
    Initialize eff_near_face_budget, eff_near_tri_budget, eff_far_tri_budget
    at declaration. They get recomputed each frame but the pause screen
    could reference them before the first frame completes.
    https://claude.ai/code/session_01CRpPKHXrP3YxsjPEStD62Z
2026-03-30 Fix tier system: distance-based classification, never skip tiers
    Previously rooms were classified by ring (ring-1=near, ring-2=far),
    causing rooms to jump from Near directly to XFar, skipping MidFar
    and Far tiers entirely. A connected room at 10000 units rendered
    the same as one at 500 units (both Near/green).
    Now: ALL rooms (except current room) classified purely by distance
    against g_dist_mid threshold:
2026-03-30 Add per-ring room count diagnostics to debug void between tiers
    Page 0 now shows: Rings:N/N/N/N/N (rooms found per ring depth).
    - Ring[0] = current + ring1 total
    - Ring[1] = new rooms found at depth 2
    - Ring[2] = depth 3
    - Ring[3] = depth 4
    - Ring[4] = depth 5
2026-03-30 Flip baked pass sort: front-to-back (closest first)
    Was back-to-front (farthest first, painter's algorithm). This meant
    the farthest room consumed the entire tri budget, and close baked
    rooms never rendered — creating the void.
    Now front-to-back: closest baked rooms render first, getting full
    budget priority. Z-fighting is possible without zbuf but acceptable
    for testing whether close baked rooms actually render.
2026-03-30 Set default budgets: tex_face=350, tex_tri=550, bkd_tri=450, draw=33000
    Per user tuning on hardware.
    https://claude.ai/code/session_01CRpPKHXrP3YxsjPEStD62Z
2026-03-30 AegisTex ROM streaming + CI4 for all tiers including Near
    Build tool:
    - build_full_rom.py now embeds .atx file in ROM with ATX_ROM_OFFSET
    - Usage: build_full_rom.py rom assets output [baked] [ci8] [atx]
    Runtime — ROM-backed CI4 loading:
    - Reads ATX1 header from ROM, gets per-tile format records
    - DMA CI4 payloads (palette + packed nibbles) from ROM
2026-03-30 Fix T3D Lara compile + rendering: vert limit, winding, camera pitch
    - Fix vertex buffer overflow: T3D max is 70, was allowing 80
    - Fix triangle winding: TR1 CW → T3D CCW (swap v1/v2)
    - Fix camera pitch: scale XZ by cos(pitch) in look_at target
    - Fix linker: --allow-multiple-definition for asset_load collision
    - Record rdpq mode + T3D draw flags inside rspq_blocks
    - Suppress unused-but-set warnings with (void) casts
2026-03-30 Complete Tier 1: tests, command ref, decoder tool, validation workflow
    Fixes from real T3D source (verified against t3d.c rspq_write calls):
    - TRI_DRAW is 2 words (was 1): W0=v0_dmem, W1=v1|v2 packed
    - DRAWFLAGS is 2 words (was 1): W0=cull_mask, W1=rdp_cmd
    - PROJ_SET is 1 word (was 2): addr in 24-bit args field
    COMMAND_REFERENCE.md: Full table with source file, line number, payload
    format, render semantic, and TR1 usage priority (P0-P3) for each of
2026-03-30 Strict VERT_LOAD validation: reject implausible input_size and address
    VERT_LOAD now requires:
    - input_size <= 1120 bytes (70 verts max = 35 packed pairs * 32)
    - input_size must be a multiple of 32 (T3DVertPacked alignment)
    - RDRAM address must be >= 0x1000 (not in MMIO space)
    - RDRAM address must be within RDRAM bounds
    Implausible VERT_LOAD commands (from misaligned scans) now
2026-03-31 Path B: CPU-side rspq intercept via SP_STATUS SIG_MORE hook
    cpu_intercept.h/c: Captures rspq commands at the CPU publish boundary.
    Hook: SP_STATUS write with SIG_MORE (signal 7) set.
    When CPU sets this, it has just written new commands to the rspq
    RDRAM buffer and is telling the RSP to process them.
    Strategy:
    1. Detect rspq buffer RDRAM addresses from DMA patterns
